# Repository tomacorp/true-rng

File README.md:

# true-rng

Hardware design to create a true-random number generator.
See https://hackaday.io/project/21054-true-random-number-generator for details.

The EAGLE files are incomplete and unchecked. I have hand-edited the symbols
and footprints based on miscellaneous EAGLE data that I have found spread around. It is not to be trusted yet! It needs checking. Also the electrical design has not been prototyped or simulated.

__noise_amplifier.xlsx__

The spreadsheet noise_amplifier.xlsx has the design equations and
documentation for the analog circuit design. I can explain the design process
in more detail in the hackaday.io project if anyone is interested.
The technique could be used to design buffer amplifiers for other types of sensors.

__vreg_local.lbr__

A local library with symbols, footprints, and maps.

__analog_rng2.sch__

The schematic so far.

__analog_rng2.brd__

The board layout, work-in-progress.

__LICENSE__

Copyright 2017 Tom Anderson

Permission is hereby granted, free of charge, to any person obtaining a copy of this software and associated documentation files (the "Software"), to deal in the Software without restriction, including without limitation the rights to use, copy, modify, merge, publish, distribute, sublicense, and/or sell copies of the Software, and to permit persons to whom the Software is furnished to do so, subject to the following conditions:

The above copyright notice and this permission notice shall be included in all copies or substantial portions of the Software.

THE SOFTWARE IS PROVIDED "AS IS", WITHOUT WARRANTY OF ANY KIND, EXPRESS OR IMPLIED, INCLUDING BUT NOT LIMITED TO THE WARRANTIES OF MERCHANTABILITY, FITNESS FOR A PARTICULAR PURPOSE AND NONINFRINGEMENT. IN NO EVENT SHALL THE AUTHORS OR COPYRIGHT HOLDERS BE LIABLE FOR ANY CLAIM, DAMAGES OR OTHER LIABILITY, WHETHER IN AN ACTION OF CONTRACT, TORT OR OTHERWISE, ARISING FROM, OUT OF OR IN CONNECTION WITH THE SOFTWARE OR THE USE OR OTHER DEALINGS IN THE SOFTWARE.

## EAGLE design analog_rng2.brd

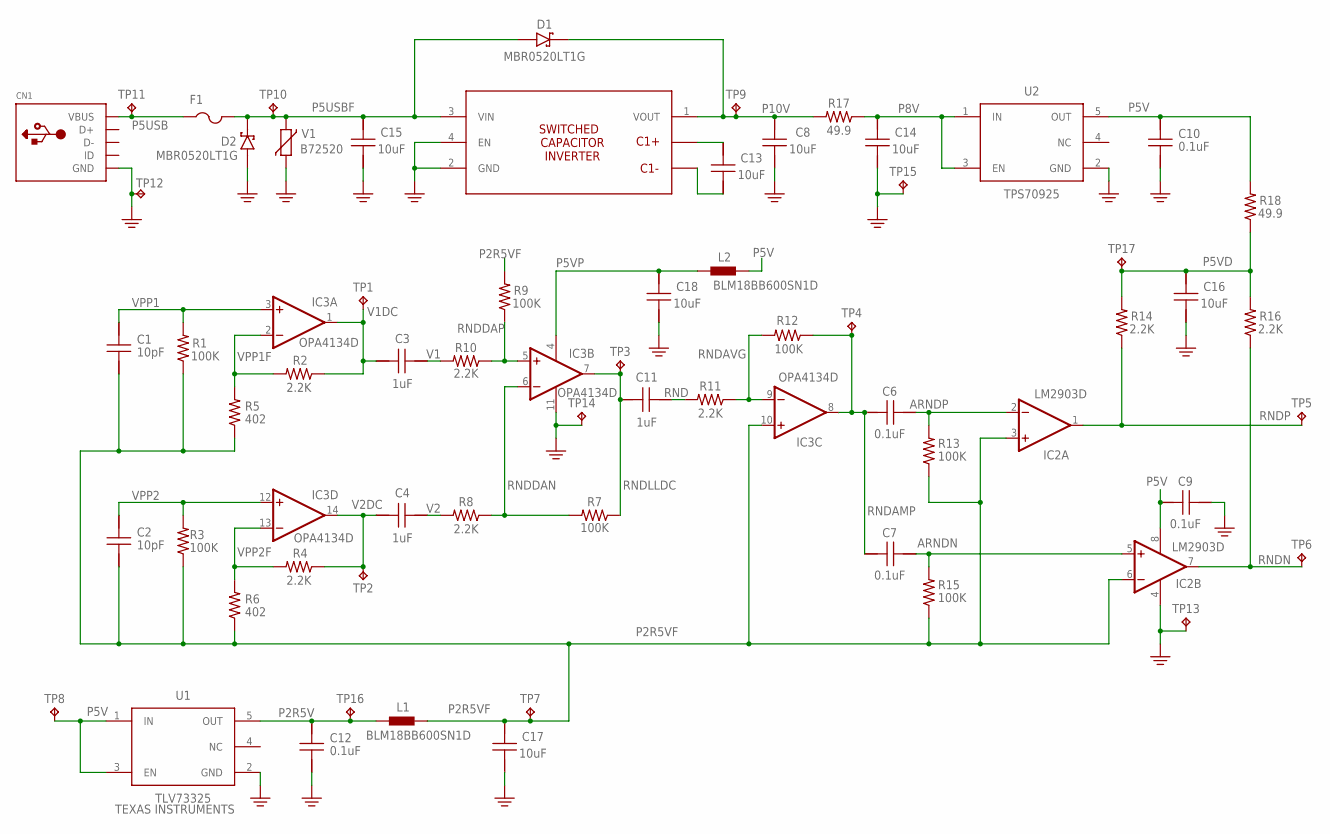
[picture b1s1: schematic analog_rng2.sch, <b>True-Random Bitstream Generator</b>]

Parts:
C1, C2: 10pF; C0603
C3, C4, C11: 1uF; C1206
C6, C7, C9, C10, C12: 0.1uF; C0603
C8, C13, C14, C15, C16, C17, C18: 10uF; C1206
CN1: USBMINIB; USB-MINIB
D1, D2: MBR0520LT1G; SOD-123
F1: PTCFUSE-1812; 1812
IC2: LM2903D; SO08
IC3: OPA4134D; SO14
L1, L2: BLM18BB600SN1D; R0805
R1, R3, R7, R9, R12, R13, R15: 100K; R1206
R2, R4, R8, R10, R11, R14, R16: 2.2K; R1206
R5, R6: 402; R1206
R17, R18: 49.9; R1206
TP1, TP2, TP3, TP4, TP5, TP6, TP7, TP8, TP9, TP10, TP11, TP12, TP13, TP14, TP15, TP16, TP17: TPPAD1-20; P1-20
U1: TLV73325; SOT23-5
U2: TPS70925; SOT23-5
U23423: LM277625; SOT23-6
V1: B72520; CT/CN1206

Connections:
ARNDN: C7.2, IC2.5 (+IN), R15.2
ARNDP: C6.2, IC2.2 (-IN), R13.2
unnamed: C13.1, U23423.5 (C1P)
unnamed: C13.2, U23423.6 (C1N)
P2R5V: C12.1, L1.1, TP16.TP, U1.5 (OUT)
P2R5VF: C1.2, C2.2, C17.1, IC2.3 (+IN), IC2.6 (-IN), IC3.10 (+IN), L1.2, R1.1, R3.1, R5.1, R6.1, R9.2, R13.1, R15.1, TP7.TP
P5USB: CN1.VBUS, F1.1, TP11.TP
P5USBF: C15.1, D1.A, D2.K, F1.2, TP10.TP, U23423.3 (VIN), V1.1
P5V: C9.1, C10.1, IC2.8 (V+), L2.2, R18.2, TP8.TP, U1.1 (IN), U1.3 (EN), U2.5 (OUT)
P5VD: C16.1, R14.2, R16.2, R18.1, TP17.TP
P5VP: C18.1, IC3.4 (V+), L2.1
P8V: C14.1, R17.1, U2.1 (IN), U2.3 (EN)
P10V: C8.1, D1.K, R17.2, TP9.TP, U23423.1 (VOUT)
PE: C8.2, C9.2, C10.2, C12.2, C14.2, C15.2, C16.2, C17.2, C18.2, CN1.GND, D2.A, IC2.4 (V-), IC3.11 (V-), TP12.TP, TP13.TP, TP14.TP, TP15.TP, U1.2 (GND), U2.2 (GND), U23423.2 (GND), U23423.4 (EN), V1.2
RND: C11.2, R11.2
RNDAMP: C6.1, C7.1, IC3.8 (OUT), R12.1, TP4.TP
RNDAVG: IC3.9 (-IN), R11.1, R12.2
RNDDAN: IC3.6 (-IN), R7.2, R8.1
RNDDAP: IC3.5 (+IN), R9.1, R10.1
RNDLLDC: C11.1, IC3.7 (OUT), R7.1, TP3.TP
RNDN: IC2.7 (OUT), R16.1, TP6.TP
RNDP: IC2.1 (OUT), R14.1, TP5.TP
V1: C3.2, R10.2
V1DC: C3.1, IC3.1 (OUT), R2.1, TP1.TP
V2: C4.2, R8.2
V2DC: C4.1, IC3.14 (OUT), R4.1, TP2.TP
VPP1: C1.1, IC3.3 (+IN), R1.2
VPP1F: IC3.2 (-IN), R2.2, R5.2
VPP2: C2.1, IC3.12 (+IN), R3.2
VPP2F: IC3.13 (-IN), R4.2, R6.2

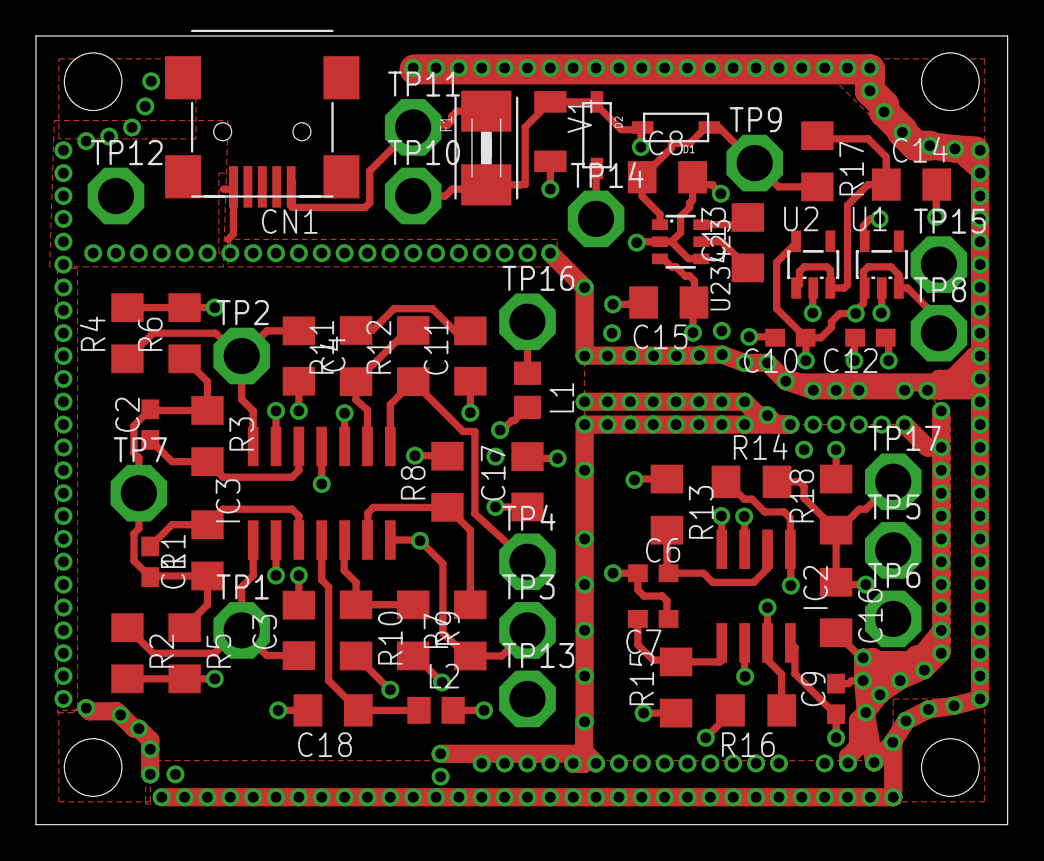
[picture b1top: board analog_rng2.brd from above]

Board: 4 copper layers, 54.0 x 43.8 mm, 64 parts (0 on the bottom side), 30 nets.

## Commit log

2017-04-09 Added link to hackaday.io project to README
2017-04-20 Initial version of design equations, schematic, and layout.
2017-04-29 More layout work done, finished first cut at copper layout
